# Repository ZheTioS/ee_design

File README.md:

# ee_design
My Embedded electronics repo

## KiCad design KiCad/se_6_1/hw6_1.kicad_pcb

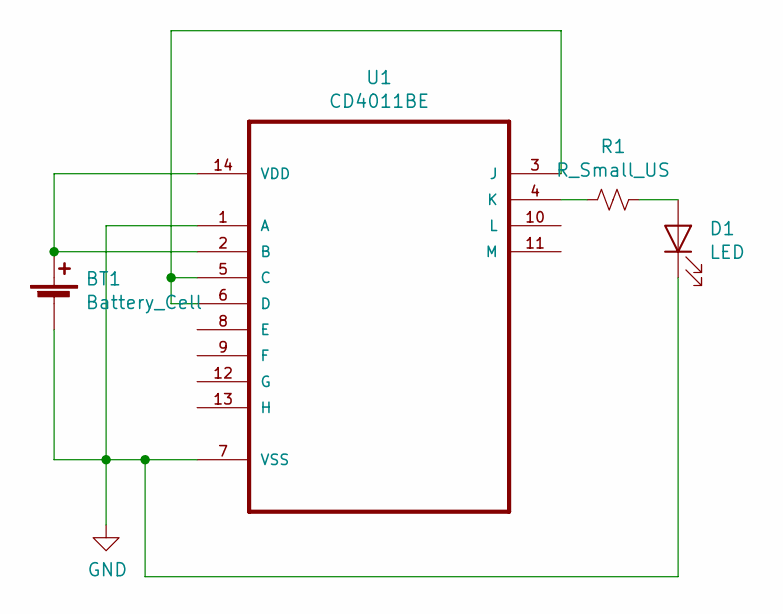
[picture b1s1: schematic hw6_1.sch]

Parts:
BT1: Battery_Cell; BatteryHolder_Keystone_3000_1x12mm
D1: LED; LED_D1.8mm_W1.8mm_H2.4mm_Horizontal_O1.27mm_Z1.6mm
R1: R_Small_US; R_0201_0603Metric
U1: CD4011BE; DIP254P762X508-14

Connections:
GND: BT1.2 (-), D1.1 (K), U1.1 (A), U1.7 (VSS)
unnamed: BT1.1 (+), U1.2 (B), U1.14 (VDD)
unnamed: D1.2 (A), R1.1
unnamed: R1.2, U1.4 (K)
unnamed: U1.3 (J), U1.5 (C), U1.6 (D)

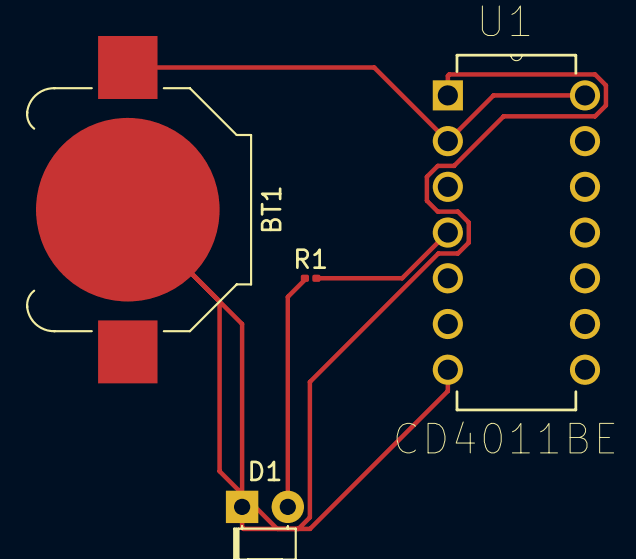
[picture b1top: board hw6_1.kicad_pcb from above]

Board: 2 copper layers, 4 parts (0 on the bottom side), 5 nets.

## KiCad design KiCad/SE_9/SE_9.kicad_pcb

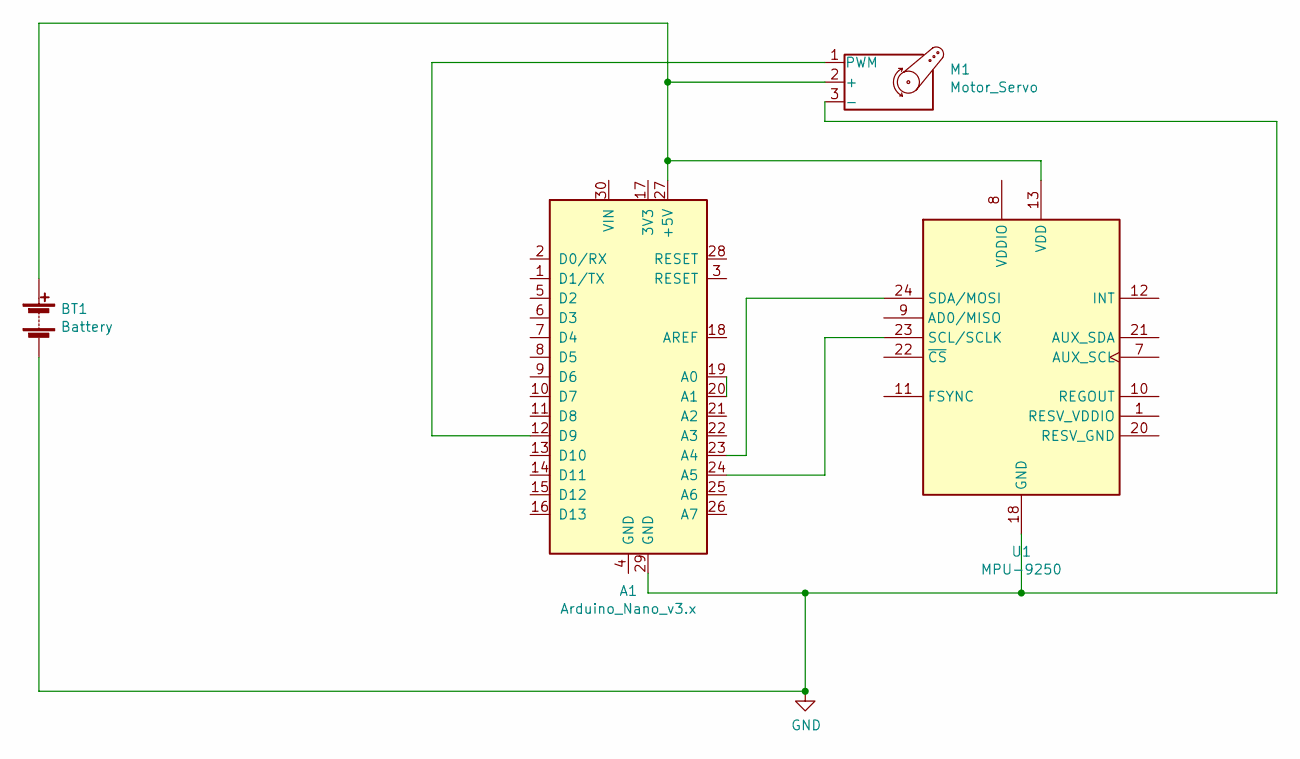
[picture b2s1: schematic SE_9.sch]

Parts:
A1: Arduino_Nano_v3.x; Arduino_Nano
BT1: Battery; BatteryHolder_Keystone_2468_2xAAA
M1: Motor_Servo; SolderWirePad_1x03_P3.81mm_Drill1.2mm
U1: MPU-9250; InvenSense_QFN-24_3x3mm_P0.4mm

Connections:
GND: A1.29 (GND), BT1.2 (-), M1.3 (-), U1.18 (GND)
unnamed: A1.12 (D9), M1.1 (PWM)
unnamed: A1.19 (A0), A1.20 (A1)
unnamed: A1.23 (A4), U1.24 (SDA/MOSI)
unnamed: A1.24 (A5), U1.23 (SCL/SCLK)
unnamed: A1.27 (+5V), BT1.1 (+), M1.2 (+), U1.13 (VDD)

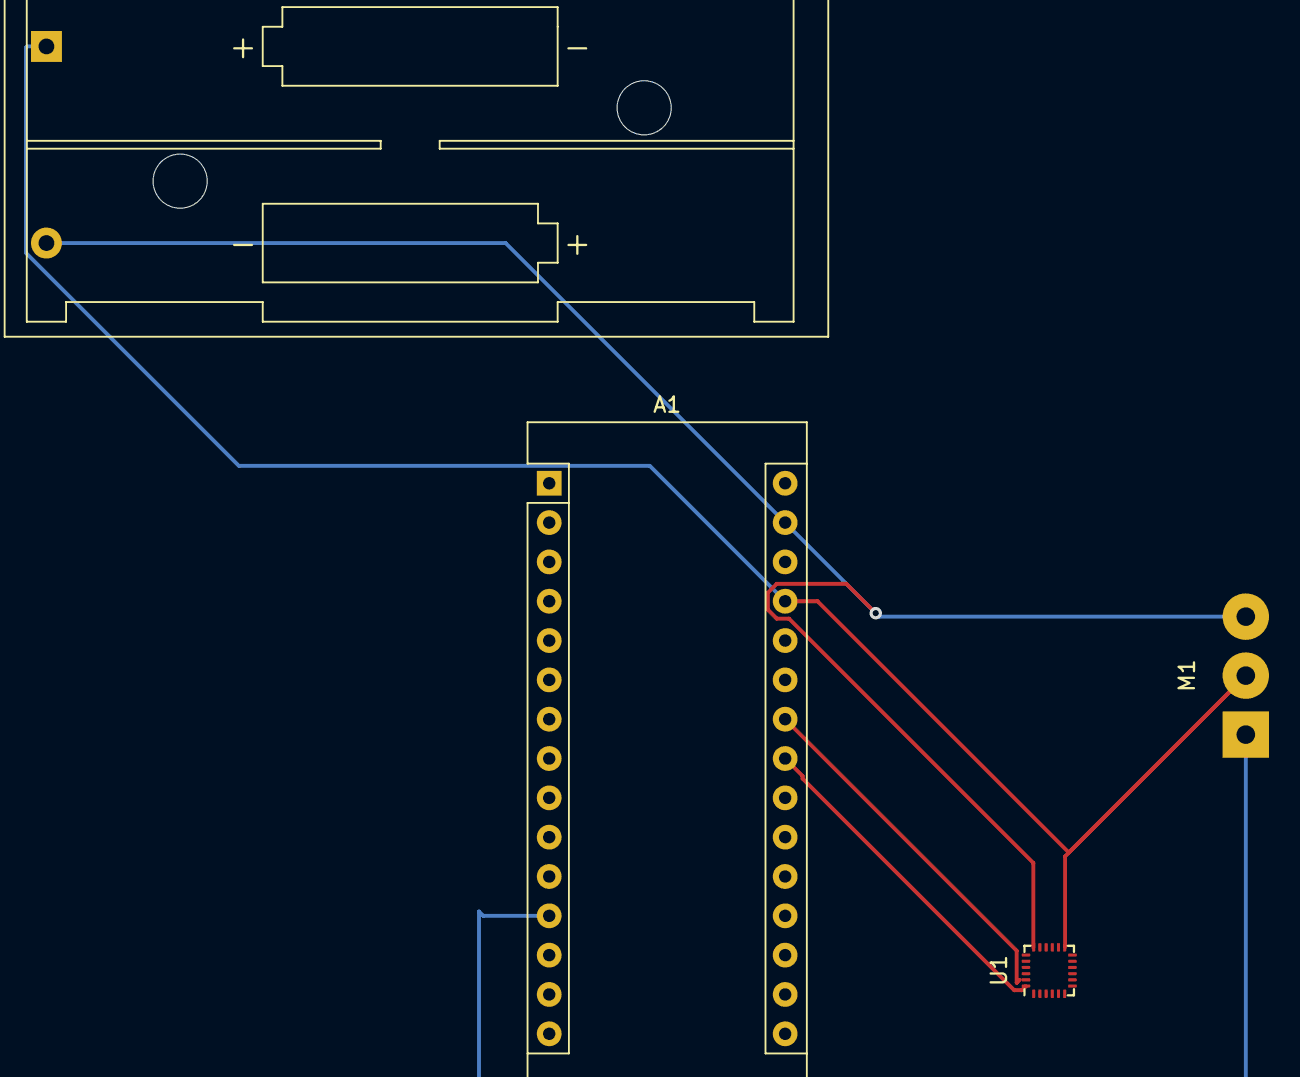
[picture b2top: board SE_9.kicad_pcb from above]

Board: 2 copper layers, 4 parts (0 on the bottom side), 6 nets.

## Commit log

2021-03-24 created repo
2021-03-28 Added FPGA_practice to repo
2021-04-20 Added notes
2021-04-20 Fixed formatting
2021-04-20 Added notes from Week 1, video 1
2021-04-20 added imgs of building blocks to notes
